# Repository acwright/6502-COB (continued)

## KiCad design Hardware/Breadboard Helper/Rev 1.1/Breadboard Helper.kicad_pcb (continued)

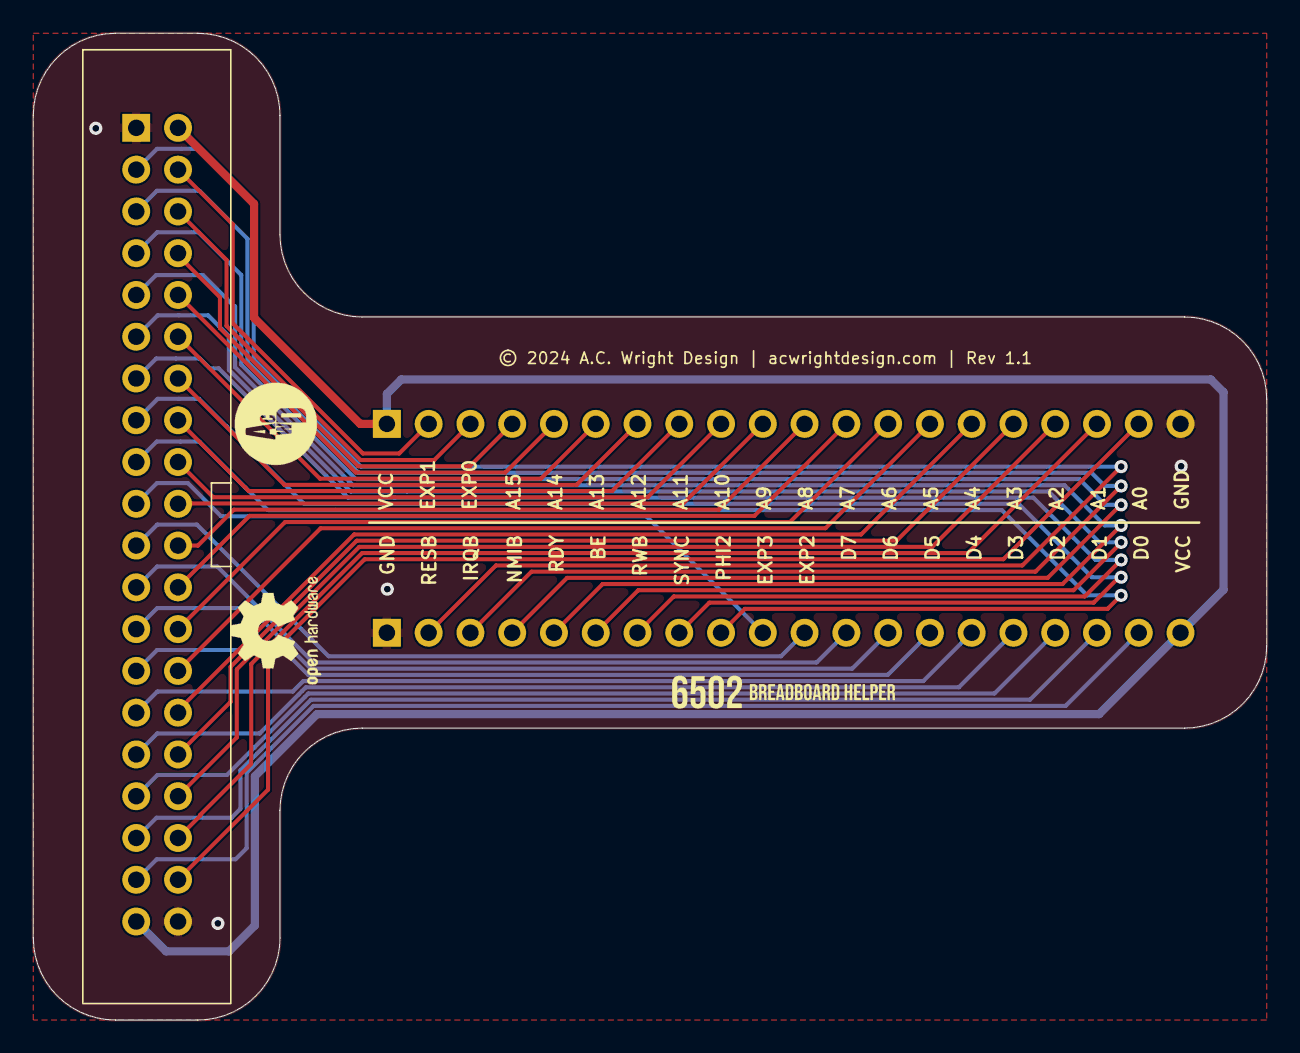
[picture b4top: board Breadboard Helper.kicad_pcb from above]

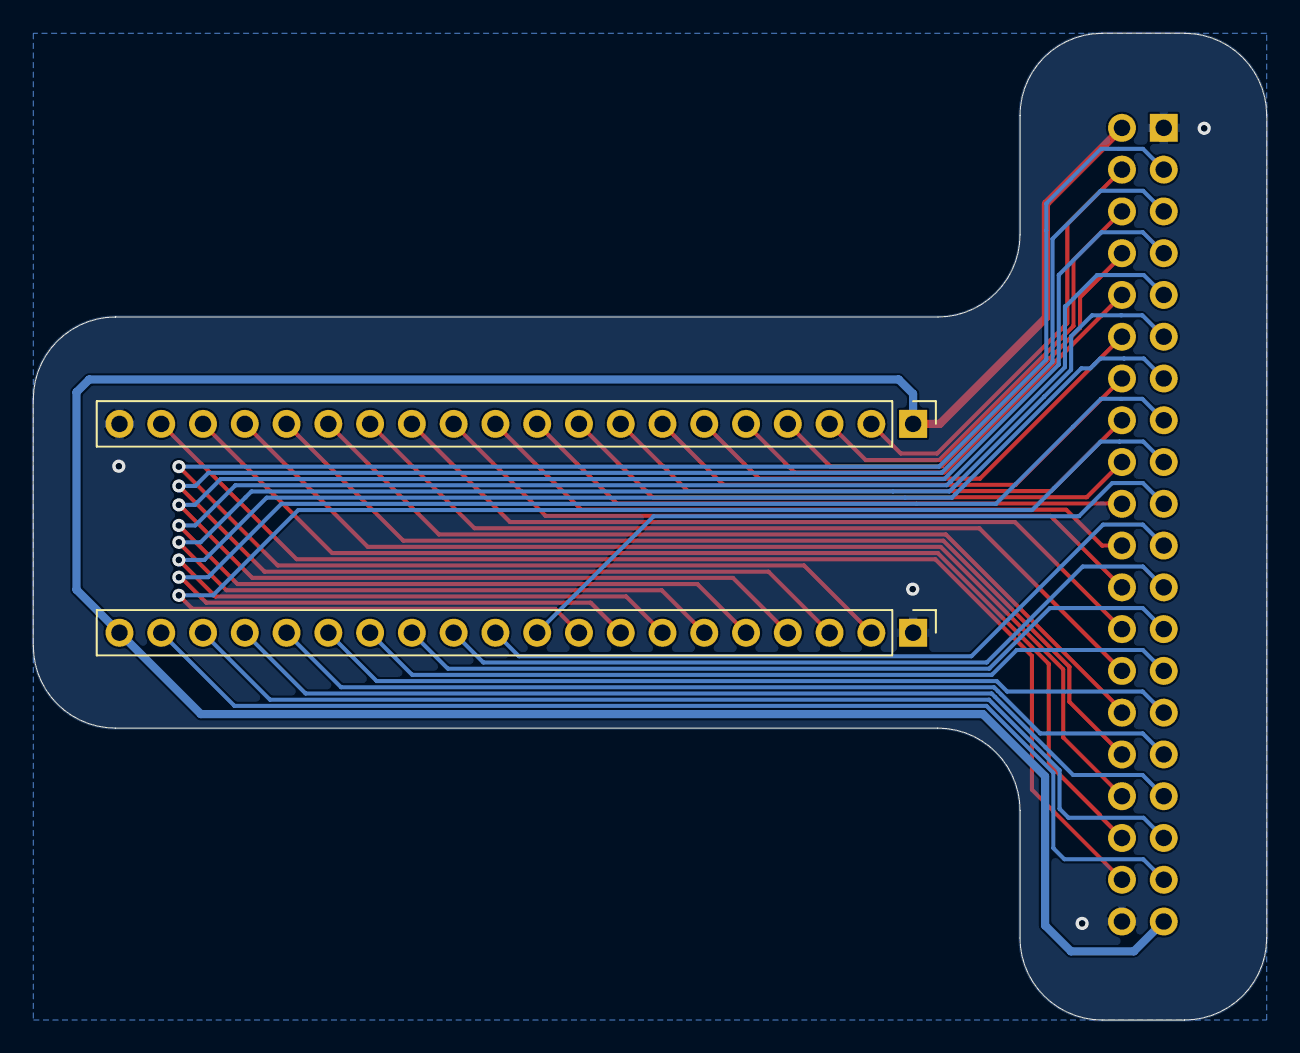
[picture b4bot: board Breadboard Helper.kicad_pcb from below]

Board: 2 copper layers, 75.0 x 60.0 mm, 3 parts (2 on the bottom side), 38 nets.

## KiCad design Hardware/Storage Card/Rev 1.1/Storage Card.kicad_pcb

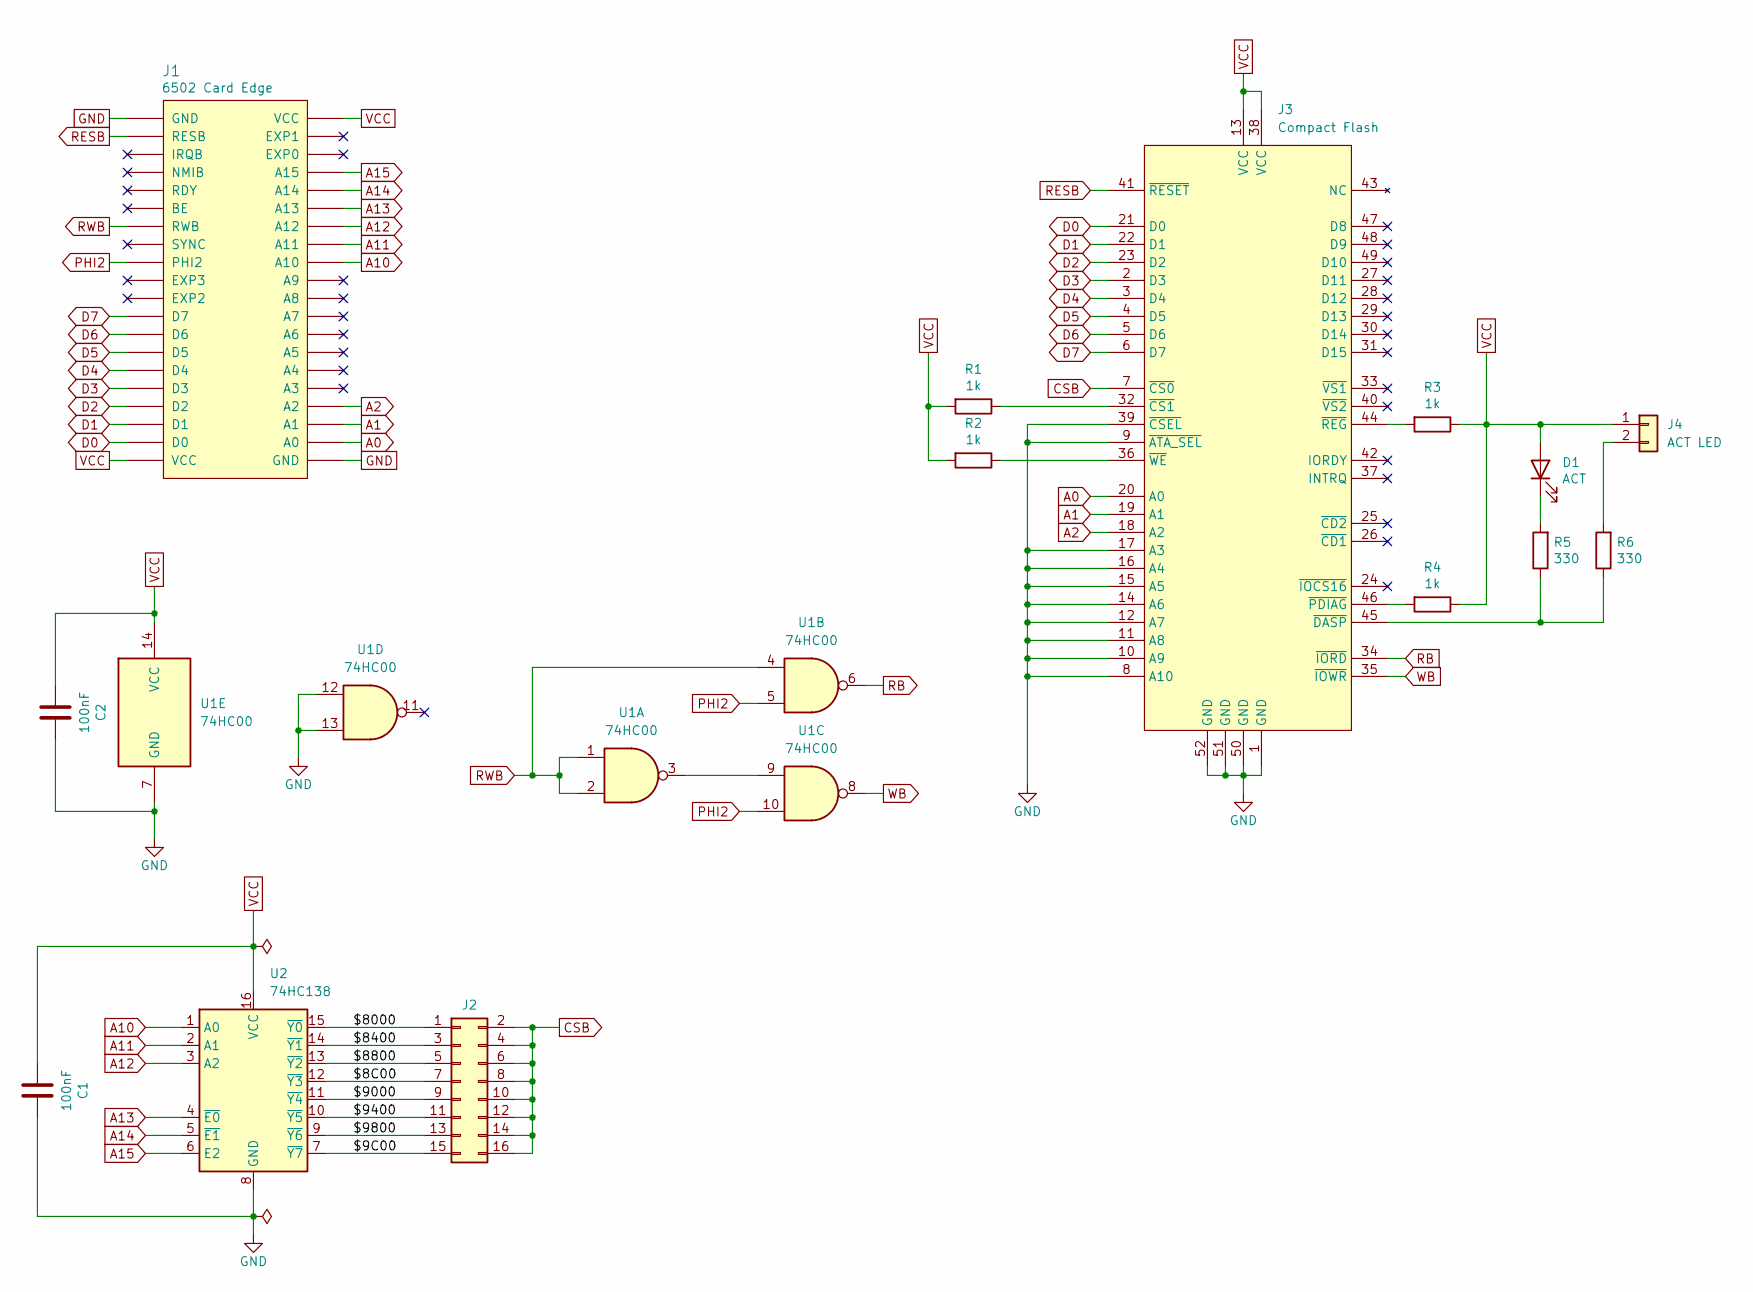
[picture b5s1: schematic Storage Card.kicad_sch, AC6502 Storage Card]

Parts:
C1, C2: 100nF; C_0805_2012Metric; LCSC C49678
D1: ACT; LED_0805_2012Metric; LCSC C2297
J1: 6502 Card Edge
J2: Conn_02x08_Odd_Even; PinHeader_2x08_P2.54mm_Vertical; Digikey S2011EC-40-ND
J3: Compact Flash; CompactFlash Socket Plated Pegs; LCSC C444350
J4: ACT LED; JST_XH_B2B-XH-A_1x02_P2.50mm_Vertical; Digikey 455-B2B-XH-A-ND
R1, R2, R3, R4: 1k; R_0805_2012Metric; LCSC C17513
R5, R6: 330; R_0805_2012Metric; LCSC C17630
U1: 74HC00; SOIC-14_3.9x8.7mm_P1.27mm; LCSC C5586
U2: 74HC138; SOIC-16_3.9x9.9mm_P1.27mm; LCSC C5602

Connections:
/$8C00: J2.7, U2.12 (~Y3)
/$9C00: J2.15, U2.7 (~Y7)
/$8000: J2.1, U2.15 (~Y0)
/$8400: J2.3, U2.14 (~Y1)
/$8800: J2.5, U2.13 (~Y2)
/$9000: J2.9, U2.11 (~Y4)
/$9400: J2.11, U2.10 (~Y5)
/$9800: J2.13, U2.9 (~Y6)
A0: J1.A0, J3.20 (A0)
A1: J1.A1, J3.19 (A1)
A2: J1.A2, J3.18 (A2)
A10: J1.A10, U2.1 (A0)
A11: J1.A11, U2.2 (A1)
A12: J1.A12, U2.3 (A2)
A13: J1.A13, U2.4 (~E0)
A14: J1.A14, U2.5 (~E1)
A15: J1.A15, U2.6 (E2)
CSB: J2.2, J2.4, J2.6, J2.8, J2.10, J2.12, J2.14, J2.16, J3.7 (~CS0)
D0: J1.D0, J3.21 (D0)
D1: J1.D1, J3.22 (D1)
D2: J1.D2, J3.23 (D2)
D3: J1.D3, J3.2 (D3)
D4: J1.D4, J3.3 (D4)
D5: J1.D5, J3.4 (D5)
D6: J1.D6, J3.5 (D6)
D7: J1.D7, J3.6 (D7)
GND: C1.2, C2.2, J1.GND, J3.1 (GND), J3.8 (A10), J3.9 (~ATA_SEL), J3.10 (A9), J3.11 (A8), J3.12 (A7), J3.14 (A6), J3.15 (A5), J3.16 (A4), J3.17 (A3), J3.39 (~CSEL), J3.50 (GND), J3.51 (GND), J3.52 (GND), U1.7 (GND), U1.12, U1.13, U2.8 (GND)
unnamed: D1.1 (K), R5.2
unnamed: J3.32 (~CS1), R1.1
unnamed: J3.45 (~DASP), R5.1, R6.1
unnamed: J3.46 (~PDIAG), R4.2
unnamed: J3.44 (~REG), R3.2
unnamed: J3.36 (~WE), R2.1
unnamed: J4.2, R6.2
unnamed: U1.3, U1.9
PHI2: J1.PHI2, U1.5, U1.10
RB: J3.34 (~IORD), U1.6
RESB: J1.RESB, J3.41 (~RESET)
RWB: J1.RWB, U1.1, U1.2, U1.4
VCC: C1.1, C2.1, D1.2 (A), J1.VCC, J3.13 (VCC), J3.38 (VCC), J4.1, R1.2, R2.2, R3.1, R4.1, U1.14 (VCC), U2.16 (VCC)
WB: J3.35 (~IOWR), U1.8

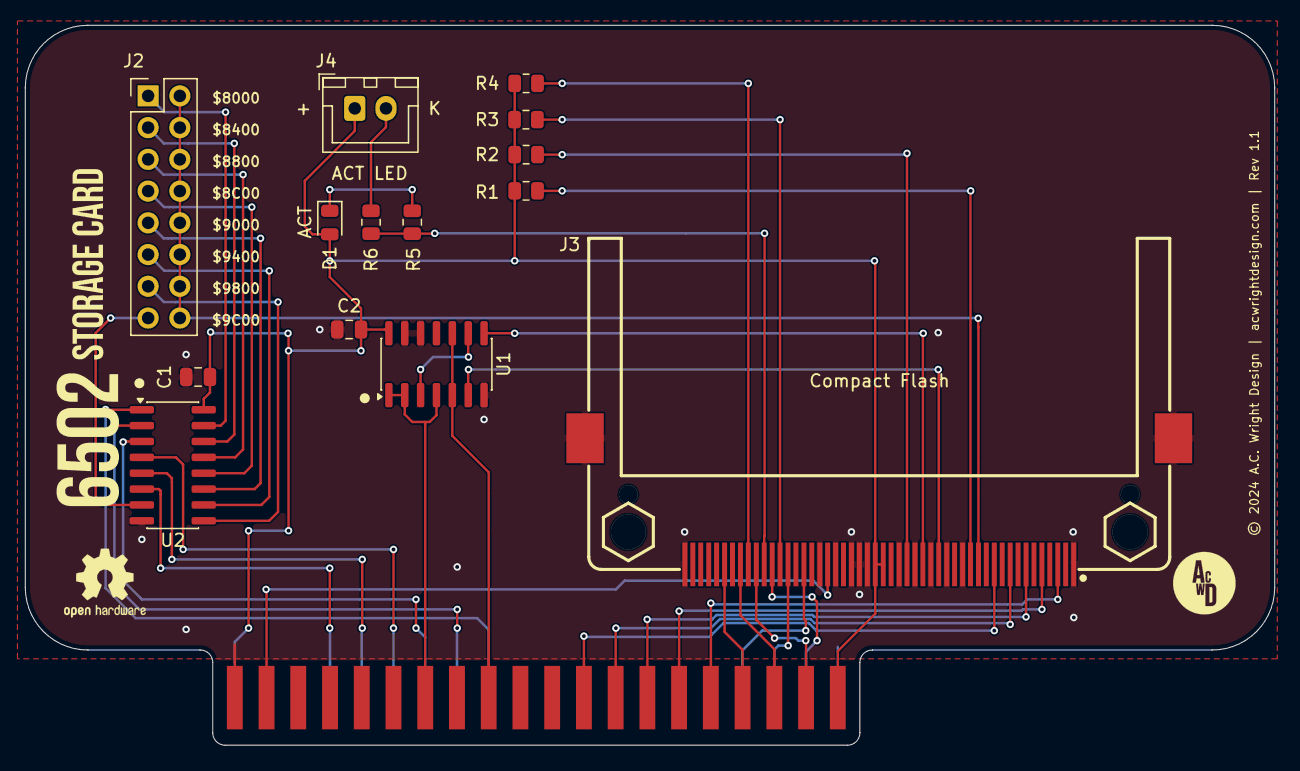
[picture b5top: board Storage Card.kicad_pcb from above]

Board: 2 copper layers, 100.0 x 57.6 mm, 15 parts (0 on the bottom side), 41 nets.

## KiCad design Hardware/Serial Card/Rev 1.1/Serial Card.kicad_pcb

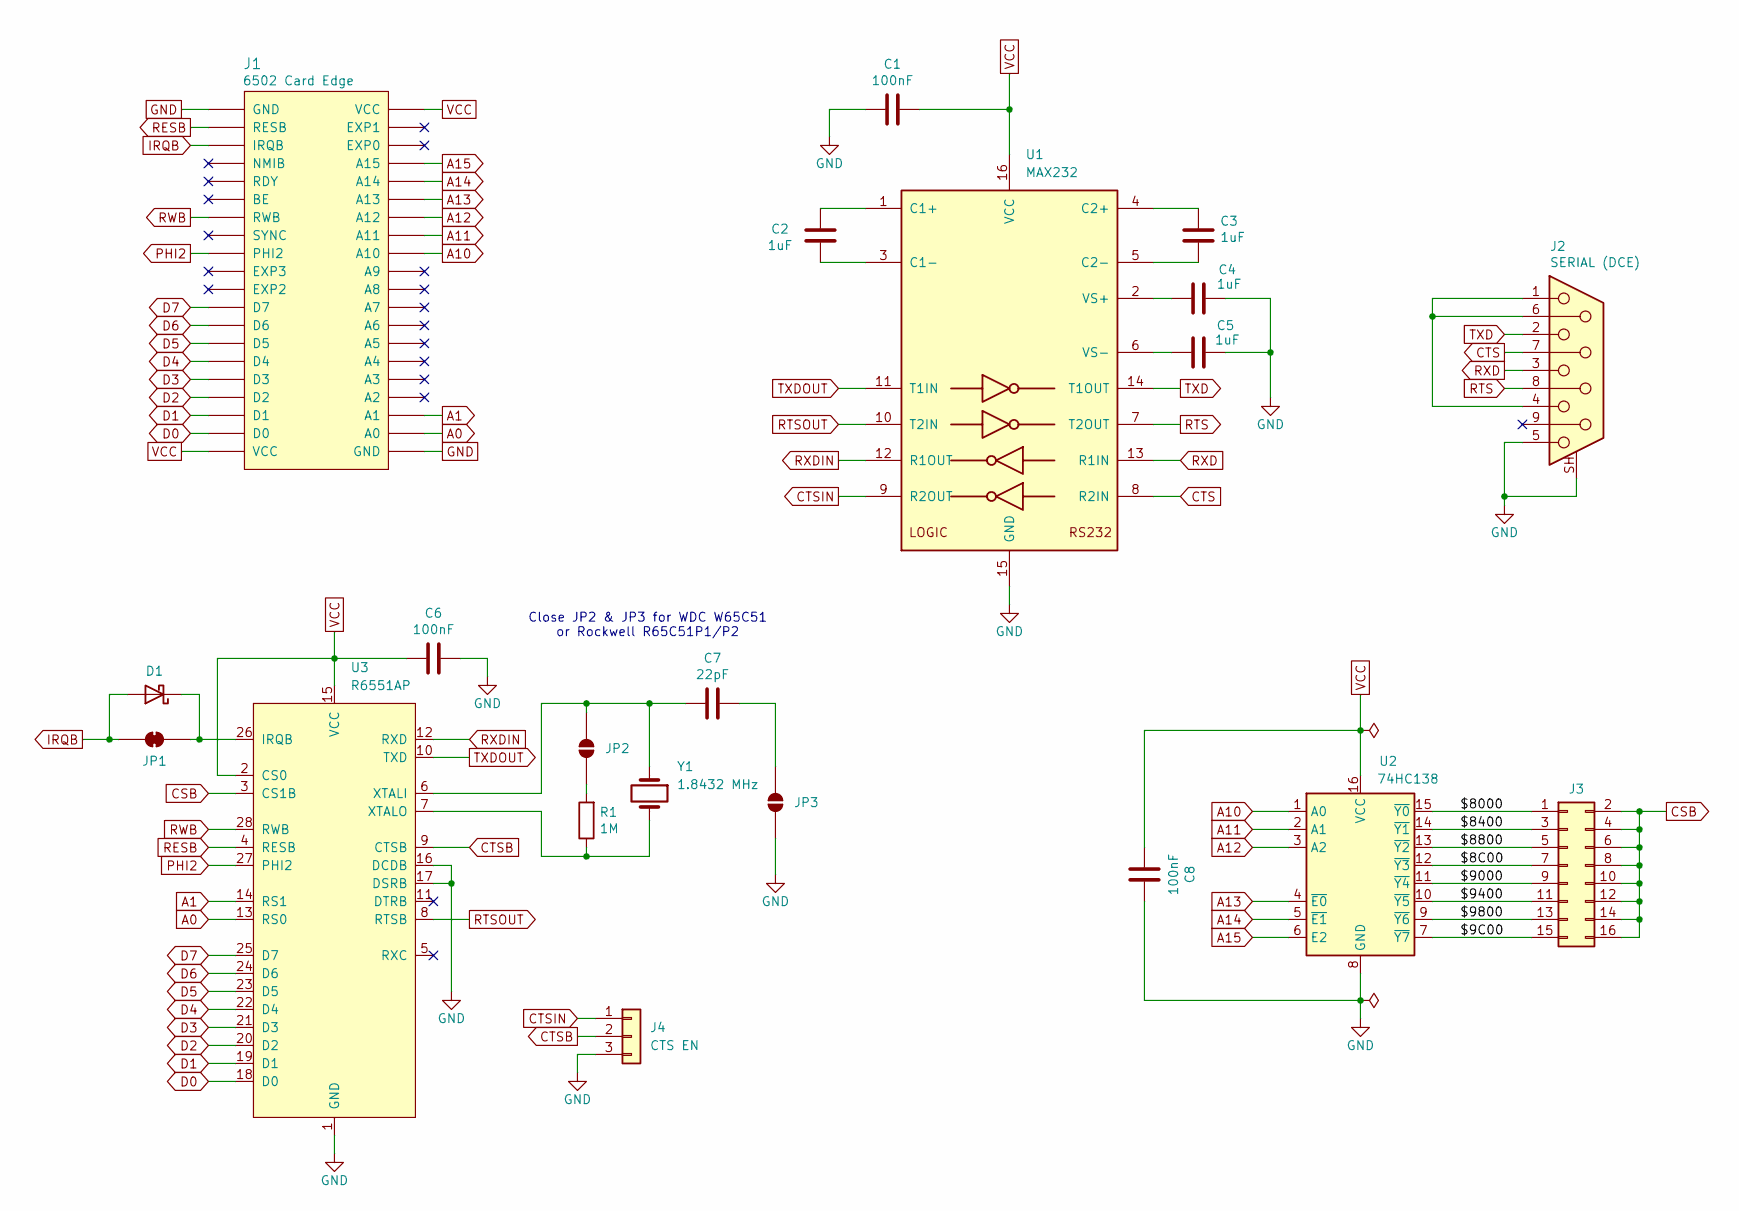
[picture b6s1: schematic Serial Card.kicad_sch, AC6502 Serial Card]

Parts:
C1, C6, C8: 100nF; C_0805_2012Metric; LCSC C49678
C2, C3, C4, C5: 1uF; C_0805_2012Metric; LCSC C28323
C7: 22pF; C_0805_2012Metric; LCSC C1804
D1: BAT85; D_DO-35_SOD27_P7.62mm_Horizontal; Digikey BAT85SCT-ND
J1: 6502 Card Edge
J2: SERIAL (DCE); DSUB-9_Socket_Horizontal_P2.77x2.84mm_EdgePinOffset7.70mm_H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; Digikey 609-1487-ND
J3: Conn_02x08_Odd_Even; PinHeader_2x08_P2.54mm_Vertical; Digikey S2011EC-40-ND
J4: CTS EN; PinHeader_1x03_P2.54mm_Vertical; Digikey S1011EC-40-ND
JP1: SolderJumper_2_Bridged; SolderJumper-2_P1.3mm_Bridged_RoundedPad1.0x1.5mm
JP2, JP3: SolderJumper_2_Open; SolderJumper-2_P1.3mm_Open_RoundedPad1.0x1.5mm
R1: 1M; R_0805_2012Metric; LCSC C17514
U1: MAX232; SOIC-16; LCSC C59824
U2: 74HC138; SOIC-16_3.9x9.9mm_P1.27mm; LCSC C5602
U3: R6551AP; DIP-28_W15.24mm_Socket_LongPads
Y1: 1.8432 MHz; Crystal_HC49-U_Vertical; Digikey 535-9009-ND

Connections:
/$8C00: J3.7, U2.12 (~Y3)
/$9C00: J3.15, U2.7 (~Y7)
/$8000: J3.1, U2.15 (~Y0)
/$8400: J3.3, U2.14 (~Y1)
/$8800: J3.5, U2.13 (~Y2)
/$9000: J3.9, U2.11 (~Y4)
/$9400: J3.11, U2.10 (~Y5)
/$9800: J3.13, U2.9 (~Y6)
A0: J1.A0, U3.13 (RS0)
A1: J1.A1, U3.14 (RS1)
A10: J1.A10, U2.1 (A0)
A11: J1.A11, U2.2 (A1)
A12: J1.A12, U2.3 (A2)
A13: J1.A13, U2.4 (~E0)
A14: J1.A14, U2.5 (~E1)
A15: J1.A15, U2.6 (E2)
CSB: J3.2, J3.4, J3.6, J3.8, J3.10, J3.12, J3.14, J3.16, U3.3 (CS1B)
CTS: J2.7, U1.8 (R2IN)
CTSB: J4.2, U3.9 (CTSB)
CTSIN: J4.1, U1.9 (R2OUT)
D0: J1.D0, U3.18 (D0)
D1: J1.D1, U3.19 (D1)
D2: J1.D2, U3.20 (D2)
D3: J1.D3, U3.21 (D3)
D4: J1.D4, U3.22 (D4)
D5: J1.D5, U3.23 (D5)
D6: J1.D6, U3.24 (D6)
D7: J1.D7, U3.25 (D7)
GND: C1.1, C4.2, C5.2, C6.2, C8.2, J1.GND, J2.5, J2.SH (PAD), J4.3, JP3.1 (A), U1.15 (GND), U2.8 (GND), U3.1 (GND), U3.16 (DCDB), U3.17 (DSRB)
IRQB: D1.2 (A), J1.IRQB, JP1.1 (A)
unnamed: D1.1 (K), JP1.2 (B), U3.26 (IRQB)
unnamed: J2.1, J2.4, J2.6
unnamed: JP2.1 (A), R1.2
unnamed: C7.2, JP2.2 (B), U3.6 (XTALI), Y1.1
unnamed: C7.1, JP3.2 (B)
unnamed: C2.1, U1.1 (C1+)
unnamed: C2.2, U1.3 (C1-)
unnamed: C3.1, U1.4 (C2+)
unnamed: C3.2, U1.5 (C2-)
unnamed: C4.1, U1.2 (VS+)
unnamed: C5.1, U1.6 (VS-)
unnamed: R1.1, U3.7 (XTALO), Y1.2
PHI2: J1.PHI2, U3.27 (PHI2)
RESB: J1.RESB, U3.4 (RESB)
RTS: J2.8, U1.7 (T2OUT)
RTSOUT: U1.10 (T2IN), U3.8 (RTSB)
RWB: J1.RWB, U3.28 (RWB)
RXD: J2.3, U1.13 (R1IN)
RXDIN: U1.12 (R1OUT), U3.12 (RXD)
TXD: J2.2, U1.14 (T1OUT)
TXDOUT: U1.11 (T1IN), U3.10 (TXD)
VCC: C1.2, C6.1, C8.1, J1.VCC, U1.16 (VCC), U2.16 (VCC), U3.2 (CS0), U3.15 (VCC)

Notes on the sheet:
Close JP2 & JP3 for WDC W65C51 or Rockwell R65C51P1/P2

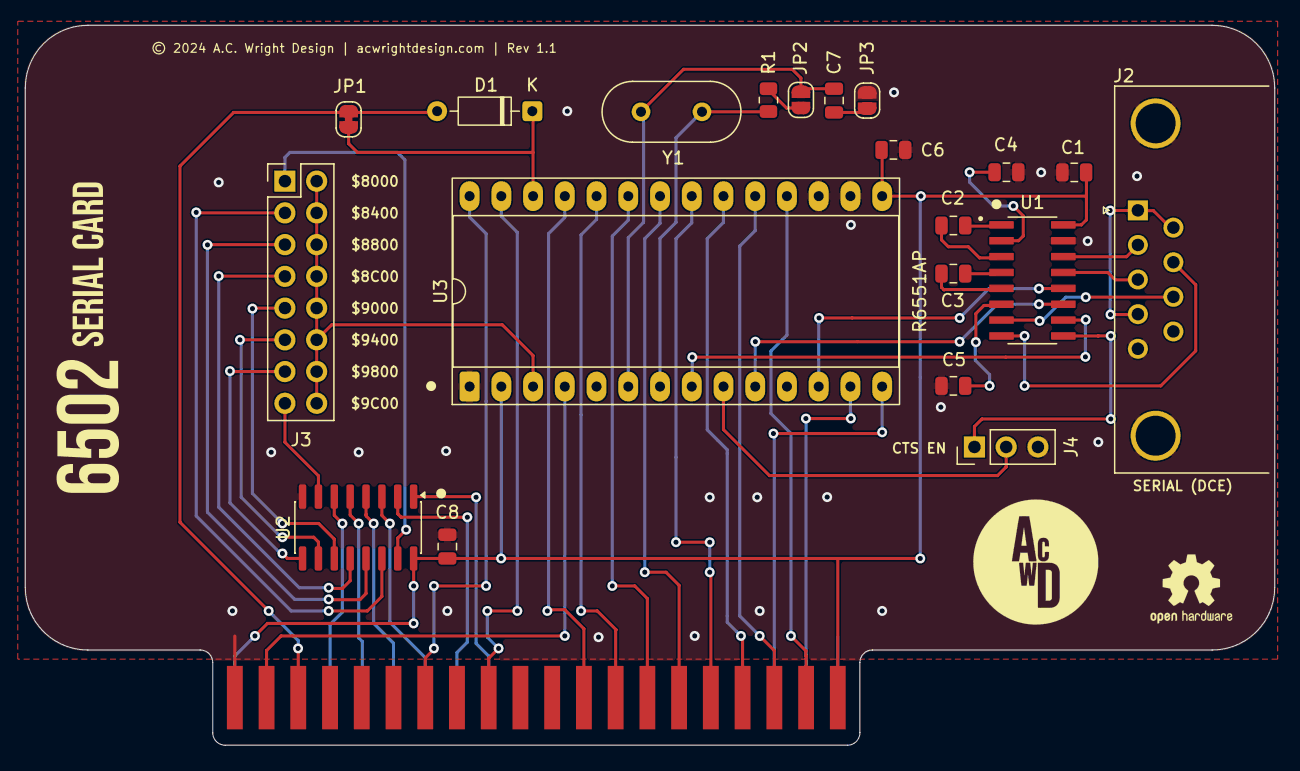
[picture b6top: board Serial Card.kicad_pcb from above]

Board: 2 copper layers, 100.0 x 57.6 mm, 21 parts (0 on the bottom side), 52 nets.

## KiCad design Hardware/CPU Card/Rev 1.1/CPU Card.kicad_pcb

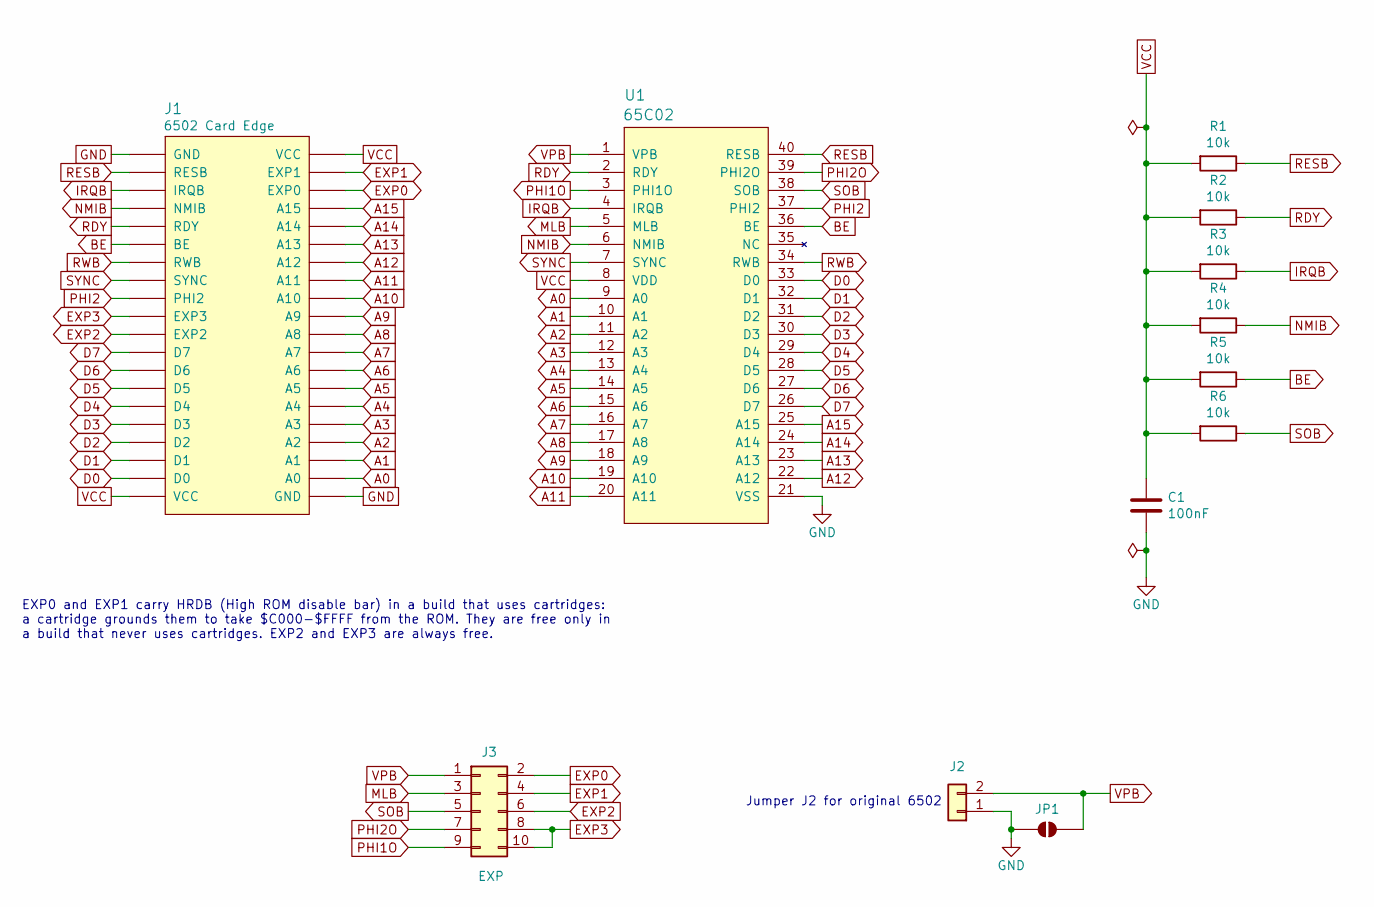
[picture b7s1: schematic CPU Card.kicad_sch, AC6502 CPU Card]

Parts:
C1: 100nF; C_0805_2012Metric; LCSC C49678
J1: 6502 Card Edge
J2: Conn_01x02; PinHeader_1x02_P2.54mm_Vertical; Digikey S1011EC-40-ND
J3: EXP; PinHeader_2x05_P2.54mm_Vertical; Digikey S2011EC-40-ND
JP1: SolderJumper_2_Open; SolderJumper-2_P1.3mm_Open_RoundedPad1.0x1.5mm
R1, R2, R3, R4, R5, R6: 10k; R_0805_2012Metric; LCSC C17414
U1: 65C02; DIP-40_W15.24mm_Socket_LongPads; Mouser 955-W65C02S6TPG-14

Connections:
A0: J1.A0, U1.9 (A0)
A1: J1.A1, U1.10 (A1)
A2: J1.A2, U1.11 (A2)
A3: J1.A3, U1.12 (A3)
A4: J1.A4, U1.13 (A4)
A5: J1.A5, U1.14 (A5)
A6: J1.A6, U1.15 (A6)
A7: J1.A7, U1.16 (A7)
A8: J1.A8, U1.17 (A8)
A9: J1.A9, U1.18 (A9)
A10: J1.A10, U1.19 (A10)
A11: J1.A11, U1.20 (A11)
A12: J1.A12, U1.22 (A12)
A13: J1.A13, U1.23 (A13)
A14: J1.A14, U1.24 (A14)
A15: J1.A15, U1.25 (A15)
BE: J1.BE, R5.1, U1.36 (BE)
D0: J1.D0, U1.33 (D0)
D1: J1.D1, U1.32 (D1)
D2: J1.D2, U1.31 (D2)
D3: J1.D3, U1.30 (D3)
D4: J1.D4, U1.29 (D4)
D5: J1.D5, U1.28 (D5)
D6: J1.D6, U1.27 (D6)
D7: J1.D7, U1.26 (D7)
EXP0: J1.EXP0, J3.2
EXP1: J1.EXP1, J3.4
EXP2: J1.EXP2, J3.6
EXP3: J1.EXP3, J3.8, J3.10
GND: C1.2, J1.GND, J2.1, JP1.1 (A), U1.21 (VSS)
IRQB: J1.IRQB, R3.1, U1.4 (IRQB)
MLB: J3.3, U1.5 (MLB)
NMIB: J1.NMIB, R4.1, U1.6 (NMIB)
PHI1O: J3.9, U1.3 (PHI1O)
PHI2: J1.PHI2, U1.37 (PHI2)
PHI2O: J3.7, U1.39 (PHI2O)
RDY: J1.RDY, R2.1, U1.2 (RDY)
RESB: J1.RESB, R1.1, U1.40 (RESB)
RWB: J1.RWB, U1.34 (RWB)
SOB: J3.5, R6.1, U1.38 (SOB)
SYNC: J1.SYNC, U1.7 (SYNC)
VCC: C1.1, J1.VCC, R1.2, R2.2, R3.2, R4.2, R5.2, R6.2, U1.8 (VDD)
VPB: J2.2, J3.1, JP1.2 (B), U1.1 (VPB)

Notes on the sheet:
EXP0 and EXP1 carry HRDB (High ROM disable bar) in a build that uses cartridges: a cartridge grounds them to take $C000-$FFFF from the ROM. They are free only in a build that never uses cartridges. EXP2 and EXP3 are always free.
Jumper J2 for original 6502

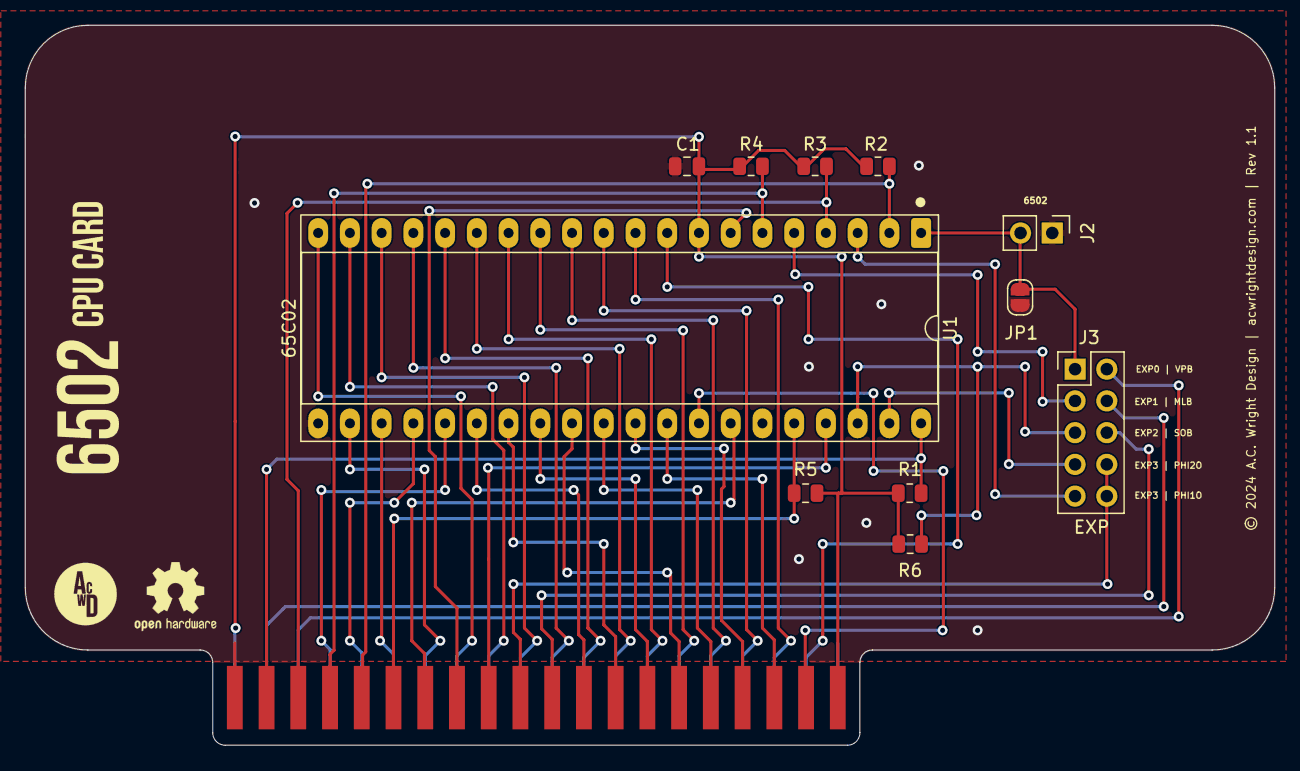
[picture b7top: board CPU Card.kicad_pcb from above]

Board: 2 copper layers, 100.0 x 57.6 mm, 12 parts (0 on the bottom side), 43 nets.

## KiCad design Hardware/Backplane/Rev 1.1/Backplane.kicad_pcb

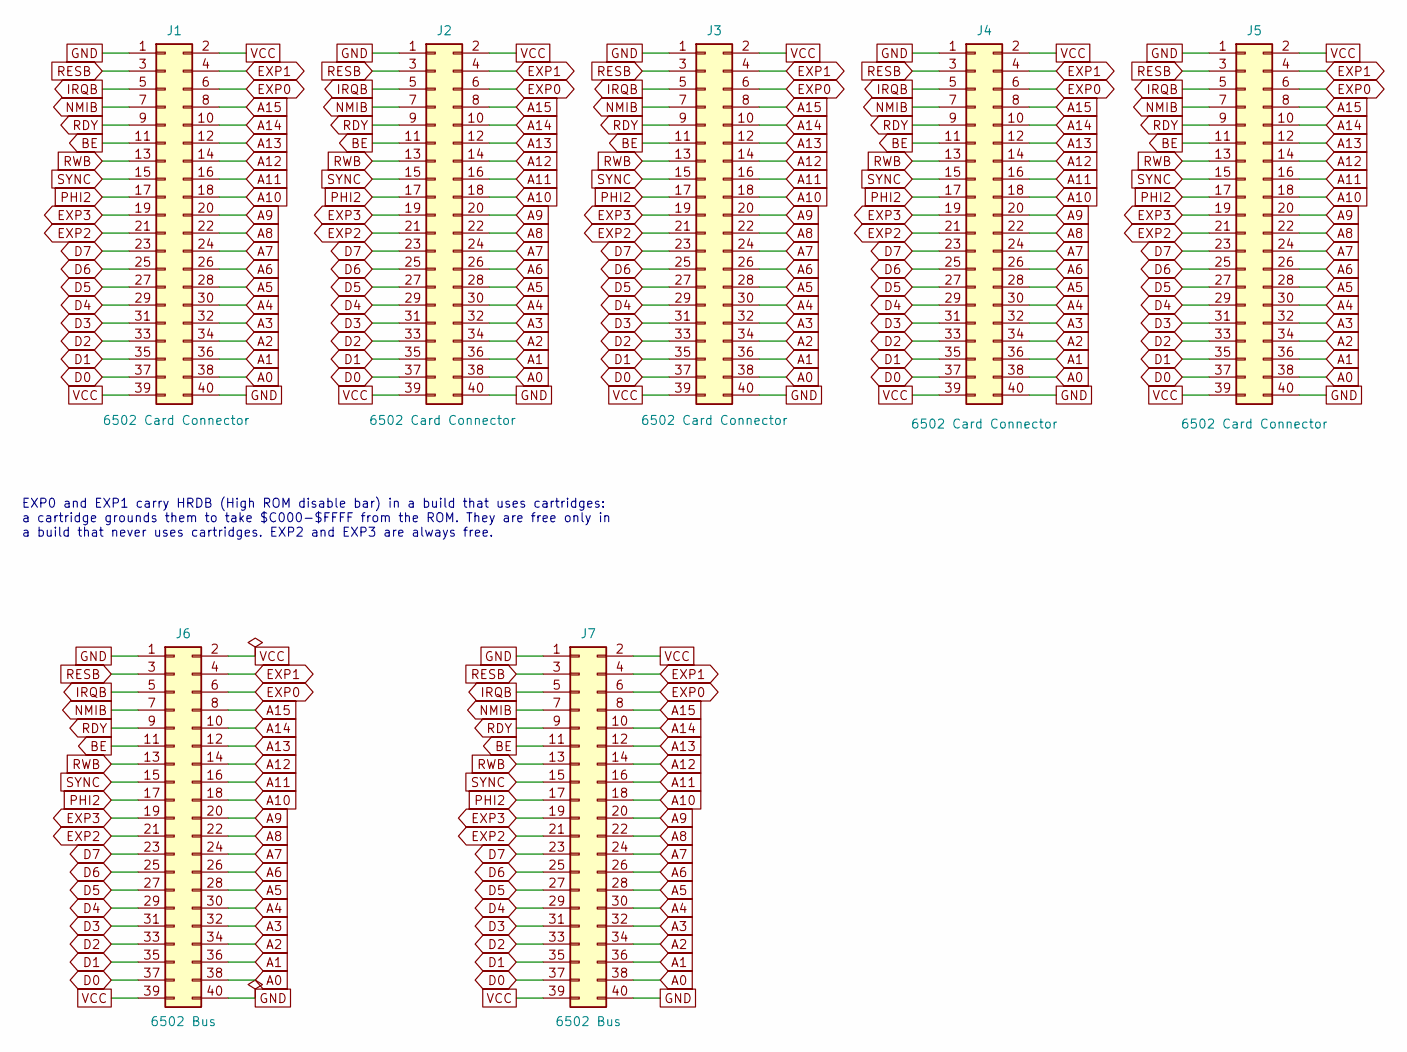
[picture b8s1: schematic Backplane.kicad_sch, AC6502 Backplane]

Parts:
J1, J2, J3, J4, J5: 6502 Card Connector; 6502 Card Slot; Mouser 571-5-5530843-4
J6, J7: 6502 Bus; 6502 Bus Connector; Digikey 732-5401-ND

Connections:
A0: J1.38, J2.38, J3.38, J4.38, J5.38, J6.38, J7.38
A1: J1.36, J2.36, J3.36, J4.36, J5.36, J6.36, J7.36
A2: J1.34, J2.34, J3.34, J4.34, J5.34, J6.34, J7.34
A3: J1.32, J2.32, J3.32, J4.32, J5.32, J6.32, J7.32
A4: J1.30, J2.30, J3.30, J4.30, J5.30, J6.30, J7.30
A5: J1.28, J2.28, J3.28, J4.28, J5.28, J6.28, J7.28
A6: J1.26, J2.26, J3.26, J4.26, J5.26, J6.26, J7.26
A7: J1.24, J2.24, J3.24, J4.24, J5.24, J6.24, J7.24
A8: J1.22, J2.22, J3.22, J4.22, J5.22, J6.22, J7.22
A9: J1.20, J2.20, J3.20, J4.20, J5.20, J6.20, J7.20
A10: J1.18, J2.18, J3.18, J4.18, J5.18, J6.18, J7.18
A11: J1.16, J2.16, J3.16, J4.16, J5.16, J6.16, J7.16
A12: J1.14, J2.14, J3.14, J4.14, J5.14, J6.14, J7.14
A13: J1.12, J2.12, J3.12, J4.12, J5.12, J6.12, J7.12
A14: J1.10, J2.10, J3.10, J4.10, J5.10, J6.10, J7.10
A15: J1.8, J2.8, J3.8, J4.8, J5.8, J6.8, J7.8
BE: J1.11, J2.11, J3.11, J4.11, J5.11, J6.11, J7.11
D0: J1.37, J2.37, J3.37, J4.37, J5.37, J6.37, J7.37
D1: J1.35, J2.35, J3.35, J4.35, J5.35, J6.35, J7.35
D2: J1.33, J2.33, J3.33, J4.33, J5.33, J6.33, J7.33
D3: J1.31, J2.31, J3.31, J4.31, J5.31, J6.31, J7.31
D4: J1.29, J2.29, J3.29, J4.29, J5.29, J6.29, J7.29
D5: J1.27, J2.27, J3.27, J4.27, J5.27, J6.27, J7.27
D6: J1.25, J2.25, J3.25, J4.25, J5.25, J6.25, J7.25
D7: J1.23, J2.23, J3.23, J4.23, J5.23, J6.23, J7.23
EXP0: J1.6, J2.6, J3.6, J4.6, J5.6, J6.6, J7.6
EXP1: J1.4, J2.4, J3.4, J4.4, J5.4, J6.4, J7.4
EXP2: J1.21, J2.21, J3.21, J4.21, J5.21, J6.21, J7.21
EXP3: J1.19, J2.19, J3.19, J4.19, J5.19, J6.19, J7.19
GND: J1.1, J1.40, J2.1, J2.40, J3.1, J3.40, J4.1, J4.40, J5.1, J5.40, J6.1, J6.40, J7.1, J7.40
IRQB: J1.5, J2.5, J3.5, J4.5, J5.5, J6.5, J7.5
NMIB: J1.7, J2.7, J3.7, J4.7, J5.7, J6.7, J7.7
PHI2: J1.17, J2.17, J3.17, J4.17, J5.17, J6.17, J7.17
RDY: J1.9, J2.9, J3.9, J4.9, J5.9, J6.9, J7.9
RESB: J1.3, J2.3, J3.3, J4.3, J5.3, J6.3, J7.3
RWB: J1.13, J2.13, J3.13, J4.13, J5.13, J6.13, J7.13
SYNC: J1.15, J2.15, J3.15, J4.15, J5.15, J6.15, J7.15
VCC: J1.2, J1.39, J2.2, J2.39, J3.2, J3.39, J4.2, J4.39, J5.2, J5.39, J6.2, J6.39, J7.2, J7.39

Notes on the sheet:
EXP0 and EXP1 carry HRDB (High ROM disable bar) in a build that uses cartridges: a cartridge grounds them to take $C000-$FFFF from the ROM. They are free only in a build that never uses cartridges. EXP2 and EXP3 are always free.

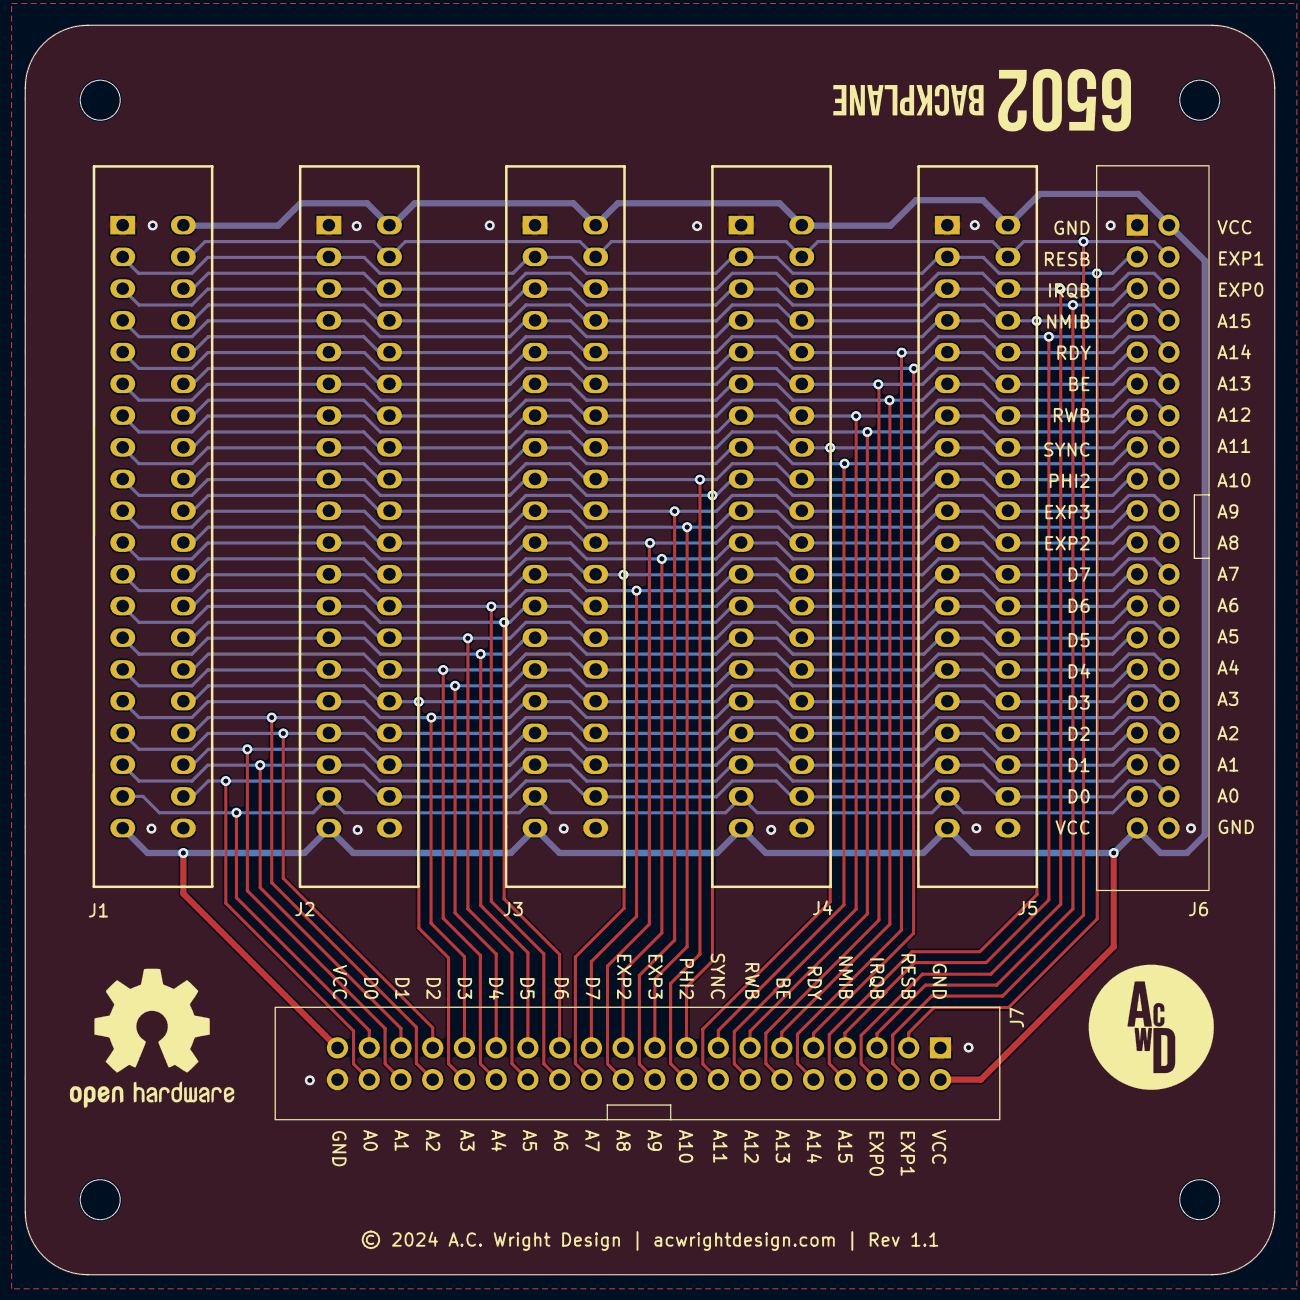
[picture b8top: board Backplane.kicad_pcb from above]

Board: 2 copper layers, 100.0 x 100.0 mm, 11 parts (0 on the bottom side), 38 nets.

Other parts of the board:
H1, H2, H3, H4: MountingHole; MountingHole_3.2mm_M3

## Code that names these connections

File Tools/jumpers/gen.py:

#!/usr/bin/env python3
"""Writes the "Jumpers" section of the README from Tools/data/jumpers.json. With --all, in all five repositories.

  gen.py            write the README
  gen.py --check    exit 1 if a README is out of date, a jumper on any revision isn't in jumpers.json, or a solder
                    jumper's "as shipped" disagrees with its footprint

jumpers.json is hand-written: what each jumper is for, how it's shipped, and what a builder does with it. The tables
and the BOM's shunt rows (Tools/bom/gen_bom.py) come from it."""
import os,sys,json,re,collections
H=os.path.dirname(os.path.abspath(__file__));sys.path.insert(0,H)
sys.path.insert(0,os.path.dirname(os.path.dirname(os.path.abspath(__file__))));import common;from common import K,SCOPE,files,load,save
J=[e for e in load('jumpers.json') if e['repo'] in SCOPE]
BEGIN='<!-- Jumpers: generated by Tools/jumpers/gen.py from Tools/data/jumpers.json. Edit that file, not this section. -->'
END='<!-- End of jumpers -->'
INTRO="""## Jumpers

Some boards have solder jumpers, and pin headers that take a shunt. The tables below give every one: what it's for, how the board is shipped, and what to do with it. The **Needed** column marks the ones that matter:

- **To run**: the board doesn't work until this is set. Set it before the first power-up.
- **For serial**, **For interrupts**, **For cartridges**: the board runs without it, but that feature doesn't.
- Blank: leave it as shipped unless you want what it offers.

Where a header needs a shunt, the board's BOM lists it.

"""
NONE="None of this repository's boards has a jumper.\n\n"
def nat(s): return [int(x) if x.isdigit() else x for x in re.split(r'(\d+)',s)]
def section(repo):
    E=[e for e in J if e['repo']==repo]
    if not E: return INTRO.split('\n\n')[0]+'\n\n'+NONE
    out=INTRO;boards=collections.OrderedDict()
    for e in sorted(E,key=lambda e:(e['board'],nat(e['revs'][0]),nat(e['refs'][0]))): boards.setdefault(e['board'],[]).append(e)
    for b,es in boards.items():
        out+=f"**{b}**\n\n| Rev | Jumper | What it's for | As shipped | What to do | Needed |\n|---|---|---|---|---|---|\n"
        for e in es:
            out+=f"| {', '.join(e['revs'])} | {', '.join(e['refs'])} | {e['what']} | {e['shipped']} | {e['do']} | {e.get('need') or ''} |\n"
        out+='\n'
    return out
def write(repo,check):
    p=f'{K}6502-{repo}/README.md';t0=open(p,encoding='utf8').read();body=BEGIN+'\n'+section(repo)+END+'\n'
    t=t0.replace('<!-- Jumpers: generated by tools/jumpers/gen.py from jumpers.json. Edit that file, not this section. -->',BEGIN)   # the marker before the tools moved into the repositories
    if BEGIN in t:
        i=t.index(BEGIN);j=t.index(END,i)+len(END)+1;new=t[:i]+body+t[j:]
    else:
        i=t.index('\n## Extra pins');j=t.index('\n## ',i+5);new=t[:j+1]+body+'\n'+t[j+1:]
        new=new.replace('- [Extra pins: `EXP0`–`EXP3` and `HRDB`](#extra-pins-exp0exp3-and-hrdb)\n','- [Extra pins: `EXP0`–`EXP3` and `HRDB`](#extra-pins-exp0exp3-and-hrdb)\n- [Jumpers](#jumpers)\n',1)
    if check: return new==t0
    if new!=t0: open(p,'w',encoding='utf8').write(new)
    return True
def coverage():
    import find
    bad=[];have=collections.defaultdict(dict)
    for e in J:
        for rev in e['revs']:
            for r in e['refs']: have[(e['repo'],e['board'],rev)][r]=e
    for k,js in find.all_jumpers().items():
        for r,(state,val) in js.items():
            e=have.get(k,{}).get(r)
            if not e: bad.append(f'{"|".join(k)} {r} ({val}) is not in jumpers.json');continue
            if state in('open','bridged'):
                s=e['shipped'].lower()
                said='bridged' if (r+' bridged') in e['shipped'] or s.startswith('bridged') else 'open' if (r+' open') in e['shipped'] or s.startswith('open') or s.startswith('both open') else None
                if said and said!=state: bad.append(f'{"|".join(k)} {r}: jumpers.json says {said}, the footprint is {state}')
    for k,rs in have.items():
        pass
    return bad
if __name__=='__main__':
    check='--check' in sys.argv;bad=[]
    for repo in SCOPE:
        if not write(repo,check): bad.append(f'{repo} README Jumpers section is out of date')
    bad+=coverage()
    for b in bad: print(b)
    print('jumpers:',len(J),'entries,',len(bad),'faults');sys.exit(1 if bad else 0)

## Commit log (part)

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2026-04-30 Schematic fix
2026-05-05 Project restructuring
2026-05-05 Remove Keypad Helper enclosure
2026-05-16 Add BOMs
2026-05-19 Add Keyboard Helper jig
2026-06-11 README fix
2026-06-15 Change pull up resistor values
2026-06-16 Add BOMs to README
2026-06-18 Add CPU Card Rev 1.1
2026-06-21 Silkscreen fix
2026-06-21 Add Backplane Pro Rev 1.1
